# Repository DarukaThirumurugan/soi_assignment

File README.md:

View this project on [CADLAB.io](https://cadlab.io/project/29089). 

# soi_assignment

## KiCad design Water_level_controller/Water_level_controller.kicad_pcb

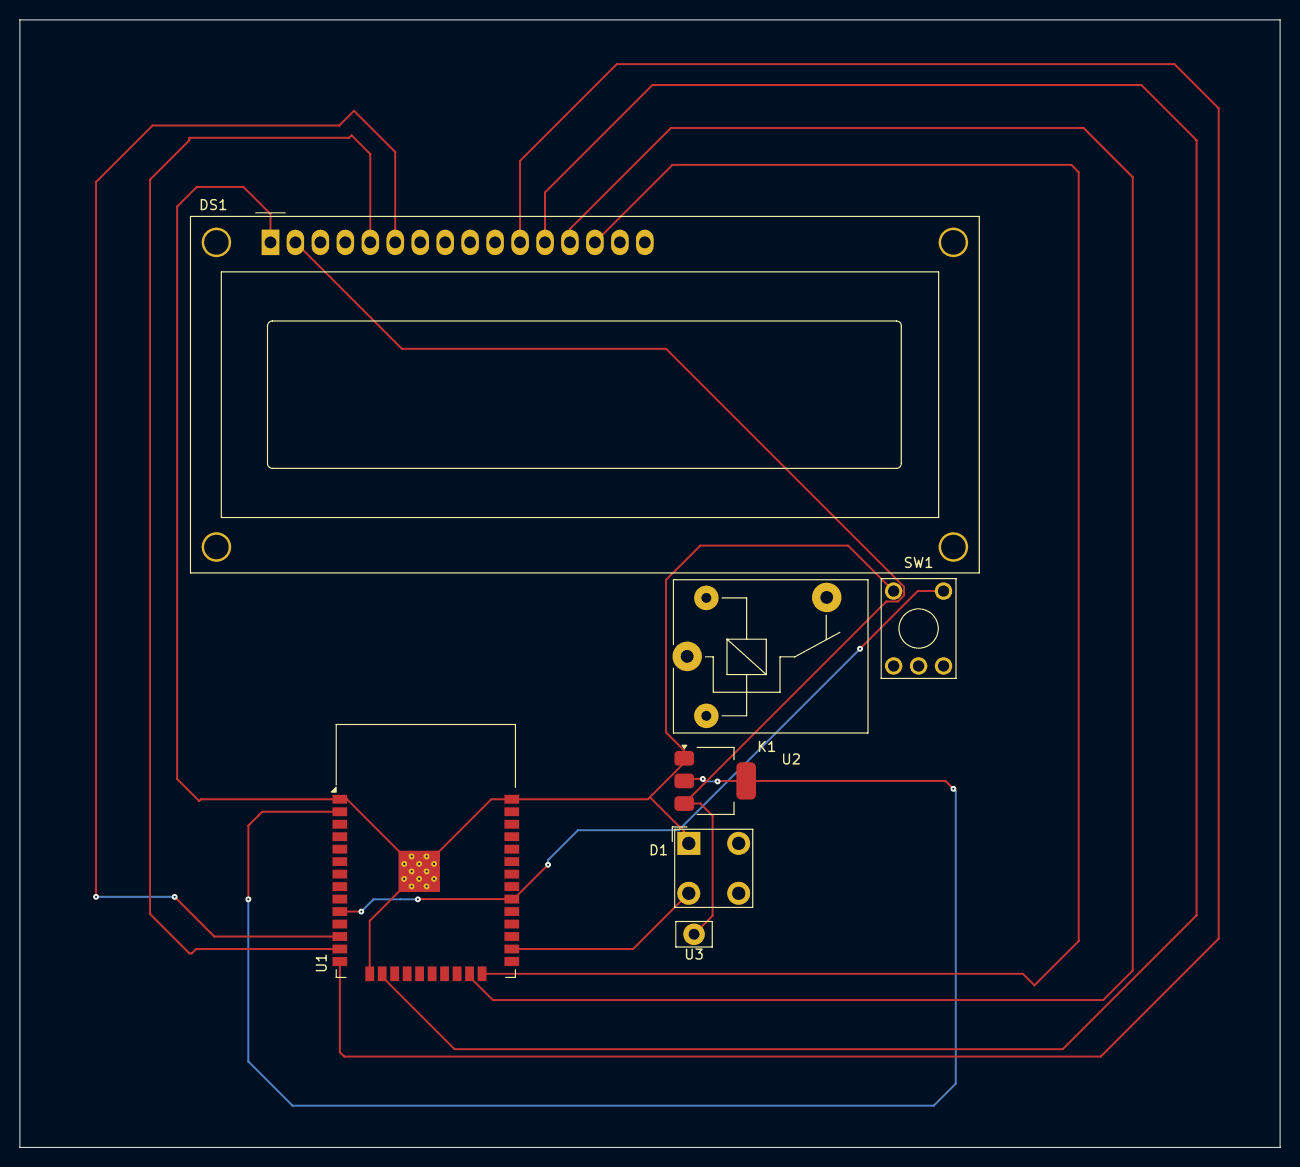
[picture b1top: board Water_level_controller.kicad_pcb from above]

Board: 2 copper layers, 128.2 x 114.8 mm, 7 parts (0 on the bottom side), 11 nets.

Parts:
D1: LED; LED_BL-FL7680RGB
DS1: WC1602A
K1: SRD-05VDC-SL-C; Relay_SPST_SANYOU_SRD_Series_Form_B
SW1: SW_Push; KSA_Tactile_SPST
U1: ESP32-WROOM-32
U2: AMS1117; SOT-223-3_TabPin2
U3: HC-SR04; Pin_D1.1mm_L10.2mm_W3.5mm_Flat

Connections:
+5V: DS1.2 (VDD), U2.3 (VI), U3.1 (VCC)
GND: D1.1 (K), DS1.1 (VSS), SW1.1, U1.1 (GND), U1.15 (GND), U1.38 (GND), U1.39 (GND), U2.1 (ADJ)
unnamed: D1.2 (A), U1.26 (IO4)
unnamed: DS1.11 (D4), U1.14 (IO12)
unnamed: DS1.12 (D5), U1.16 (IO13)
unnamed: DS1.13 (D6), U1.23 (IO15)
unnamed: DS1.14 (D7), U1.24 (IO2)
unnamed: DS1.6 (E), U1.12 (IO27)
unnamed: DS1.5 (R/W), U1.13 (IO14)
unnamed: SW1.2, U1.10 (IO25), U1.30 (IO18)
unnamed: U1.2 (VDD), U2.2 (VO)

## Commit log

2025-03-30 Assignment Commit
2025-03-30 Backlink to CADLAB.io has been added.
